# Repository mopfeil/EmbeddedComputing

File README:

Lecture Embedded Computing - script and slides
===============================================================================

Build
  make            builds docu.pdf (script) and slides.pdf (slides)
  make script     only the script
  make slides     only the slides
  make clean      removes LaTeX build artifacts

Structure

  docu.tex (script, A4)        slides.tex (slides, A5 landscape)
        \                        /
         +---- preamble.tex ----+      common packages, listings setup
         +---- mathmacros.tex --+      macros (\bi, \ite, \defn, \qbox, ...)
         |                      +--    mathmacros-sl.tex (slide overrides)
         +---- text.tex --------+      list of chapters
                  |
   Intro, Modelling, Cyber_Physical_Systems, Processors, Programming,
   Interfaces, tcp_ip_serial, OperatingSystems   (*.tex)

Script vs. slides
  \nsl{...}   text only in the script
  \os{...}    text only on the slides (typically \os{\newpage} = slide break)

Figures live in figures/; the figures of tcp_ip_serial.tex in images/.
Runnable examples live in examples/<chapter>/ (each with its own README.md):
  modelling/    ch. 2  coffee machine FSM, C and Rust (Pico)
  cps/          ch. 3  Modelica models, Python simulation (plots of ch. 3)
  processors/   ch. 4  one C function compiled for AVR, Cortex-M0+/M4, RISC-V
  programming/  ch. 5  assembly from C and Rust, Rust library with tests,
                       MicroPython, Python
  interfaces/   ch. 6  GPIO, IRQ, PWM, ADC, UART, I2C, SPI, watchdog (Pico)
  networking/   ch. 7  Wi-Fi, HTTP, NTP, MQTT (ESP32-C3), sockets on the PC
  os/           ch. 8  FreeRTOS and Embassy tasks, queues, mutex (ESP32-C3)
C examples run in the browser on https://wokwi.com, Rust examples are built
with cargo and simulated with the Wokwi extension for VS Code.

Literature: refs.bib (all entries are listed in script and slides).
All sources are UTF-8 with LF line endings.

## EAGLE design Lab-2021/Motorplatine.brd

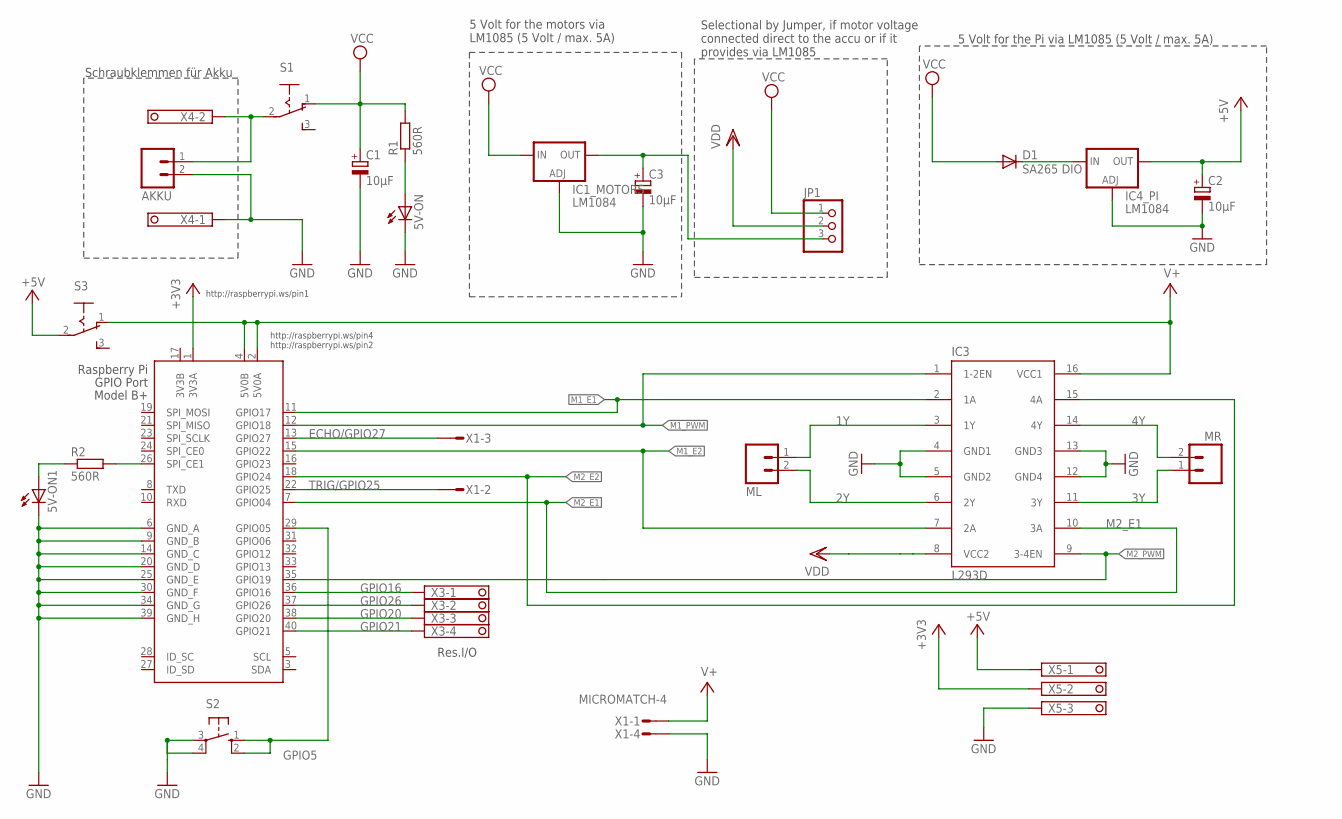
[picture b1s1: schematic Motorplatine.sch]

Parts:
5V-ON, 5V-ON1: LEDSML1206; SML1206
AKKU: MA02; 02PA
C1, C2, C3: 10μF; CT3528
D1: SA265 DIO; MELF-MLL41
IC1_MOTORS, IC4_PI: LM1084; 317TL
IC3: L293D; DIL16
JP1: PINHD-1X3; 1X03
ML: MA02; 02PA
MR: MA02; 02PA
R1, R2: 560R; R1206
S1, S3: 255SB
S2: 10-XX; B3F-10XX
X1: MICROMATCH-4
X2: RASPI_GPIO_B+#_PIN; RASPI_GPIO_B+_PIN
X3: 1751264
X4: 1751248
X5: 1751251

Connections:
1Y: IC3.3 (1Y), ML.1
2Y: IC3.6 (2Y), ML.2
3V3B: X2.17 (3V3B)
3Y: IC3.11 (3Y), MR.1
4Y: IC3.14 (4Y), MR.2
+3V3: X2.1 (3V3A), X5.2
+5V: C2.+, IC4_PI.2 (OUT), S3.2, X5.1
ECHO/GPIO27: X1.3, X2.13 (GPIO27)
GND: 5V-ON.C, 5V-ON1.C, AKKU.2, C1.-, C2.-, C3.-, IC1_MOTORS.1 (ADJ), IC3.4 (GND1), IC3.5 (GND2), IC3.12 (GND4), IC3.13 (GND3), IC4_PI.1 (ADJ), S2.3, S2.4 (P1), X1.4, X2.6 (GND_A), X2.9 (GND_B), X2.14 (GND_C), X2.20 (GND_D), X2.25 (GND_E), X2.30 (GND_F), X2.34 (GND_G), X2.39 (GND_H), X4.1, X5.3
GPIO5: S2.1 (S), S2.2 (S1), X2.29 (GPIO05)
GPIO16: X2.36 (GPIO16), X3.1
GPIO20: X2.38 (GPIO20), X3.3
GPIO21: X2.40 (GPIO21), X3.4
GPIO26: X2.37 (GPIO26), X3.2
M1_E1: IC3.2 (1A), X2.11 (GPIO17)
M1_E2: IC3.7 (2A), X2.15 (GPIO22)
M1_PWM: IC3.1 (1-2EN), X2.12 (GPIO18)
M2_E1: IC3.10 (3A), X2.7 (GPIO04)
M2_E2: IC3.15 (4A), X2.18 (GPIO24)
M2_PWM: IC3.9 (3-4EN), X2.35 (GPIO19)
unnamed: 5V-ON1.A, R2.1
unnamed: R2.2, X2.26 (SPI_CE1)
unnamed: C3.+, IC1_MOTORS.2 (OUT), JP1.3
unnamed: AKKU.1, S1.2, X4.2
unnamed: D1.C, IC4_PI.3 (IN)
unnamed: 5V-ON.A, R1.1
TRIG/GPIO25: X1.2, X2.22 (GPIO25)
V+: IC3.16 (VCC1), S3.1 (O), X1.1, X2.2 (5V0A), X2.4 (5V0B)
VCC: C1.+, D1.A, IC1_MOTORS.3 (IN), JP1.1, R1.2, S1.1 (O)
VDD: IC3.8 (VCC2), JP1.2

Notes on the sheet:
Schraubklemmen für Akku
Selectional by Jumper, if motor voltage connected direct to the accu or if it provides via LM1085
5 Volt for the motors via LM1085 (5 Volt / max. 5A)
5 Volt for the Pi via LM1085 (5 Volt / max. 5A)
Res.I/O
http://raspberrypi.ws/pin4 http://raspberrypi.ws/pin2
http://raspberrypi.ws/pin1

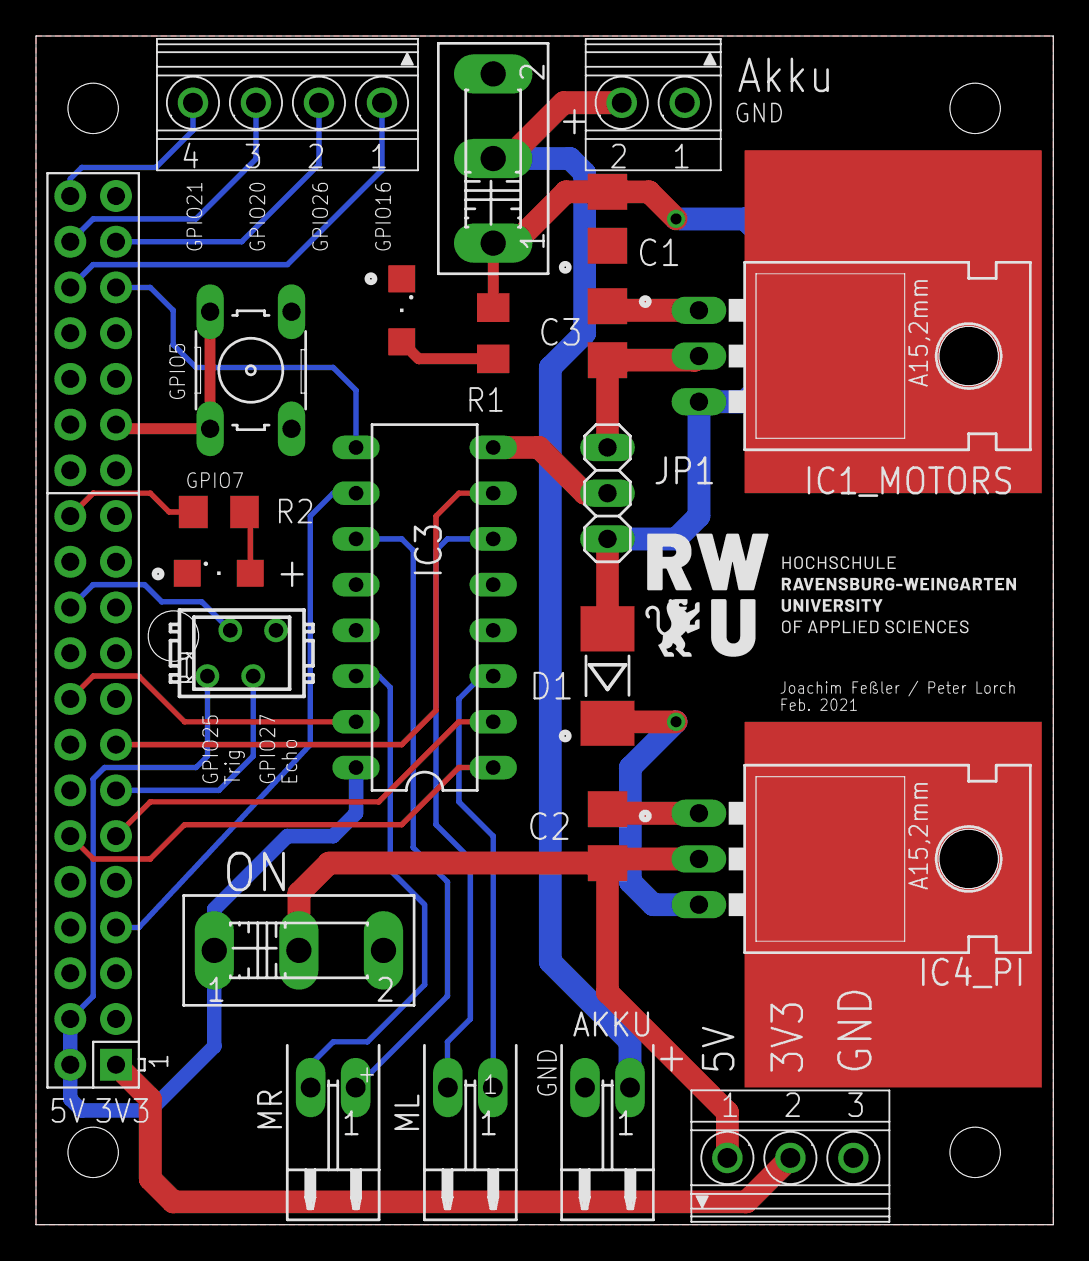
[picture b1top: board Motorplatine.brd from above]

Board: 2 copper layers, 56.5 x 66.0 mm, 23 parts (0 on the bottom side), 29 nets.

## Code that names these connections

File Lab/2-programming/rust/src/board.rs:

//! Given: the hardware of the ET1 lab set-up (see diagram.json).
//! You do not need to change this file.
//!
//!   GP7  red LED (high = on)          GP5  START button to GND (low = pressed)
//!   GP18 ENA  left motor PWM          GP19 ENB  right motor PWM   (PWM slice 1, 1 kHz)
//!   GP17 IN1  left direction A        GP20 IN3  right direction A
//!   GP16 IN2  left direction B        GP21 IN4  right direction B
//!   GP0/GP1  UART0, 115200 baud, to the serial monitor

use embedded_hal::delay::DelayNs;
use embedded_hal::digital::InputPin;
use rp_pico::hal::fugit::RateExtU32;
use rp_pico::hal::gpio::{self, DynPinId, FunctionSioInput, FunctionSioOutput, Pin, PullDown, PullUp};
use rp_pico::hal::pwm::{FreeRunning, Pwm1, Slice};
use rp_pico::hal::uart::{DataBits, Enabled, StopBits, UartConfig, UartPeripheral};
use rp_pico::hal::{self, Clock, pac};

pub type OutPin = Pin<DynPinId, FunctionSioOutput, PullDown>;
pub type InPin = Pin<DynPinId, FunctionSioInput, PullUp>;
pub type Uart = UartPeripheral<
    Enabled,
    pac::UART0,
    (
        Pin<gpio::bank0::Gpio0, gpio::FunctionUart, PullDown>,
        Pin<gpio::bank0::Gpio1, gpio::FunctionUart, PullDown>,
    ),
>;

pub struct Board {
    pub led: OutPin,
    pub button: InPin,
    /// PWM slice 1: `pwm.channel_a` drives ENA (left), `pwm.channel_b` ENB (right).
    /// Duty cycle with embedded-hal's SetDutyCycle: `set_duty_cycle_percent(0..=100)`.
    pub pwm: Slice<Pwm1, FreeRunning>,
    pub in1: OutPin,
    pub in2: OutPin,
    pub in3: OutPin,
    pub in4: OutPin,
    /// For `writeln!(board.uart, "...")` (needs `use core::fmt::Write`).
    pub uart: Uart,
    timer: hal::Timer,
}

impl Board {
    pub fn init() -> Board {
        let mut pac = pac::Peripherals::take().unwrap();
        let mut watchdog = hal::Watchdog::new(pac.WATCHDOG);
        let clocks = hal::clocks::init_clocks_and_plls(
            rp_pico::XOSC_CRYSTAL_FREQ, pac.XOSC, pac.CLOCKS, pac.PLL_SYS, pac.PLL_USB,
            &mut pac.RESETS, &mut watchdog,
        )
        .ok()
        .unwrap();
        let timer = hal::Timer::new(pac.TIMER, &mut pac.RESETS, &clocks);
        let sio = hal::Sio::new(pac.SIO);
        let pins = rp_pico::Pins::new(pac.IO_BANK0, pac.PADS_BANK0, sio.gpio_bank0, &mut pac.RESETS);

        let uart_pins = (
            pins.gpio0.into_function::<gpio::FunctionUart>(),
            pins.gpio1.into_function::<gpio::FunctionUart>(),
        );
        let uart = UartPeripheral::new(pac.UART0, uart_pins, &mut pac.RESETS)
            .enable(
                UartConfig::new(115_200.Hz(), DataBits::Eight, None, StopBits::One),
                clocks.peripheral_clock.freq(),
            )
            .unwrap();

        let slices = hal::pwm::Slices::new(pac.PWM, &mut pac.RESETS);
        let mut pwm = slices.pwm1;
        pwm.set_div_int(125); // 125 MHz / 125 = 1 MHz counter clock
        pwm.set_top(999); // 1000 counts -> 1 kHz
        pwm.enable();
        pwm.channel_a.output_to(pins.gpio18);
        pwm.channel_b.output_to(pins.gpio19);

        Board {
            led: pins.gpio7.into_push_pull_output().into_dyn_pin(),
            button: pins.gpio5.into_pull_up_input().into_dyn_pin(),
            pwm,
            in1: pins.gpio17.into_push_pull_output().into_dyn_pin(),
            in2: pins.gpio16.into_push_pull_output().into_dyn_pin(),
            in3: pins.gpio20.into_push_pull_output().into_dyn_pin(),
            in4: pins.gpio21.into_push_pull_output().into_dyn_pin(),
            uart,
            timer,
        }
    }

    /// Milliseconds since start.
    pub fn millis(&self) -> u64 {
        self.timer.get_counter().ticks() / 1000
    }

    pub fn delay_ms(&mut self, ms: u32) {
        self.timer.delay_ms(ms);
    }

    /// Raw level of the button, without debouncing: true = pressed.
    pub fn button_down(&mut self) -> bool {
        self.button.is_low().unwrap()
    }
}

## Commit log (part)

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2021-03-08 Update README.md
    Added Dropbox Link für Image
2021-03-19 Added RT1 Descriptions
2021-05-15 Solution to Task added
2021-05-15 task_5 uploaded
2021-05-17 Task_6 uploaded
2021-05-17 task
2021-05-17 Updates from Overleaf
2021-05-17 Solution edit possible
2021-05-17 Edited solution
2021-05-17 Task_6 added
2021-05-17 Updated Task5
2021-05-30 Python codes added
2021-05-30 Report Completed
2021-05-31 Update meas.py : Optimized detection
2021-05-31 speeds changed
2021-05-31 New data sets collected
2021-09-29 Create ET1
